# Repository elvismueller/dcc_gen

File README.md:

dcc_gen
=======

Simple DCC generator for ATMega8 (V2, schematics and board) and ATMega32 (V3-5, only protoypes) to control small isolated layouts.

Features:
- RS232 Interface (9600 baud) for debugging and simple control (use an normal USB to RS232 converter)
- Heartbeat LED should blink roundabout every 2 sek, fast blinking if waiting for second key
- Connect simple switches (ATMega8 10 inputs | ATMega32 4 groups, 20 Inputs, 80 switches in total)
- Support start-end logic and searches for routes in the internal memory
- Setup for USBProg ISP-Interface adapter by www.embeded-projecs.de (for any other modify platformio.ini)

Toolchain (PlatformIo)
- install Visual Studio Code
- install PlatformIO Extension via Extension Manager (left toolbar). Wait til its installed completely (Icon appears in left toolbar)!
- clone, pull and open workspace dcc_gen
- Build it (bottom bar tick icon)Toolchain
- install driver for USBasp with Zadig (https://zadig.akeo.ie/)
  == USBasp (HK version with fischl.de FW): more or less working with: WinUSB v6.1.7600 and libusb_win32, somehow unreliable
  == USBProg 3 running with modified config (check for platformio.ini)
- use "Upload" in Tasks by click on the PlatformIo Icon (Note: returns an error even if the upload was succesful), check avrdude output!

Toolchain Linux (_Archive)
- sudo aptitude install avr-libc avrdude gcc-avr simulavr
- check/use the Makefile

Kown issues: 
- it is NOT a central unit, just a simple generator
- a lot of hardcoded stuff, no SW to init the memory
- bare metal (no Ardunio Code)
- explizit build for either ATMega8 oder ATMega32
- tested only with a few turnout decoder (Claus Illchmann, LDT Datentechnik) some decoder are not working (QDecoder). 
- like almost all motorshields based on this hardware the generatet DCC signal is not recommended for train control. 
- the ATMega8 is very limited in memory and far less verbose (no help etc.)

Helpers
- read fuses with avrdude: .\avrdude -c avrispmkii -p atmega8 -U lfuse:r:-:i -v
- http://www.engbedded.com/fusecalc
- https://hendrich.org/blogs/mikrocontroller/atmega-644-fuses-setzen/
- programm size: C:/Users/EMM/.platformio/packages/toolchain-atmelavr/bin/avr-size --mcu=atmega8 -C .\firmware.elf

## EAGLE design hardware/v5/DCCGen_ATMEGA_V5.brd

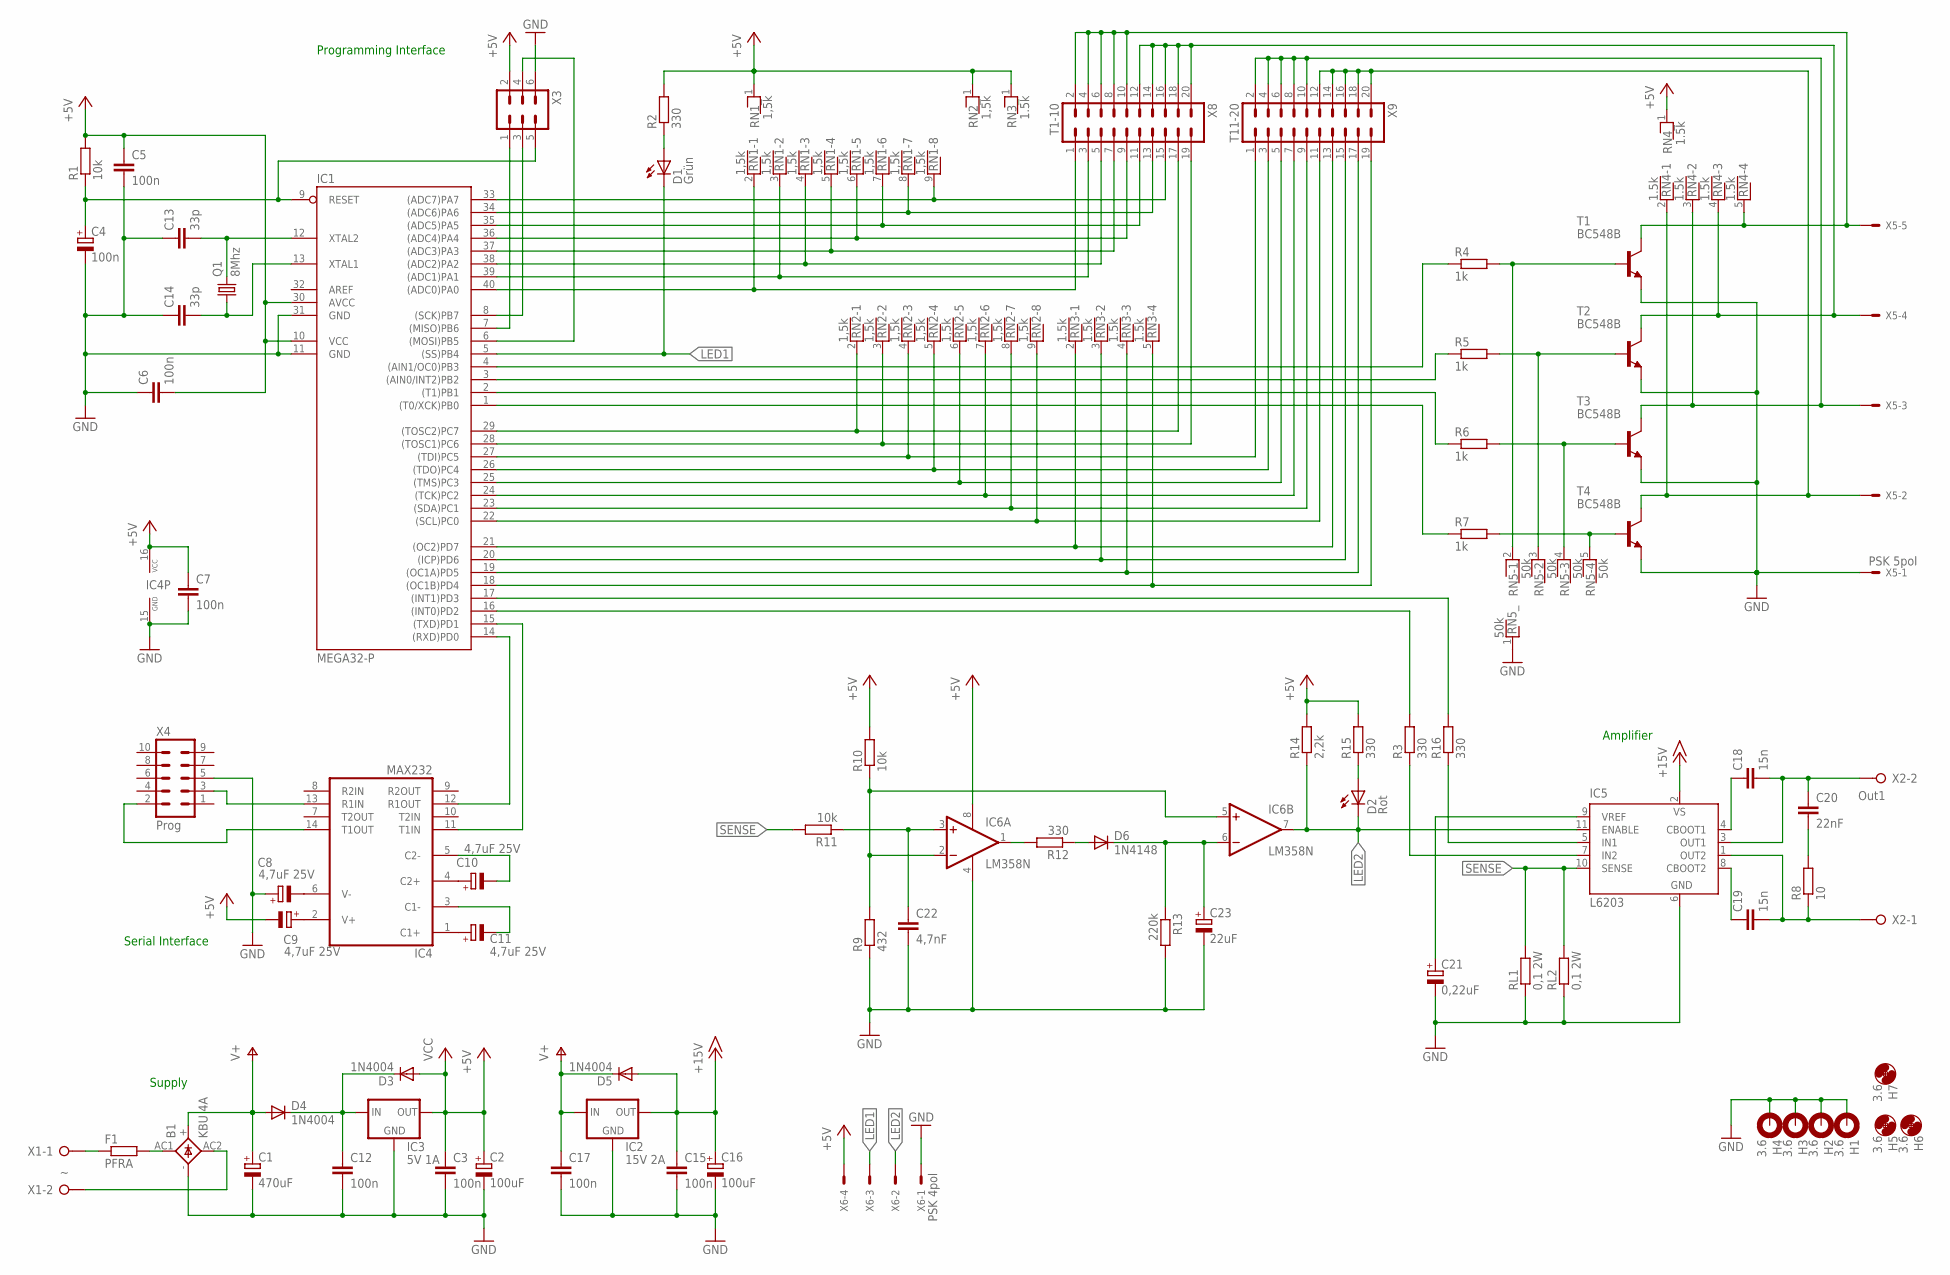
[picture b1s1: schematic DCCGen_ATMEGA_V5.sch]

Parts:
B1: KBU 4A; KBU
C1: 470uF; E5-13
C2, C16: 100uF; E2,5-7
C3, C5, C6, C7, C12, C15, C17: 100n; C025-025X050
C4: 100n; E2,5-5
C8, C9, C10, C11: 4,7uF 25V; E2,5-6E
C13, C14: 33p; C025-025X050
C18, C19: 15n; C025-025X050
C20: 22nF; C025-025X050
C21: 0,22uF; E2-5
C22: 4,7nF; C025-025X050
C23: 22uF; E2-5
D1: Grün; LED3MM
D2: Rot; LED3MM
D3, D4, D5: 1N4004; DO41-10
D6: 1N4148; DO35-10
F1: PFRA; 0204/5
H1, H2, H3, H4: 3.6; 3,6-PAD
H5, H6, H7: 3.6; 3,6
IC1: MEGA32-P; DIL40
IC2: 15V 2A; 78XXS
IC3: 5V 1A; 78XXS
IC4: MAX232; DIL16
IC5: L6203; MULTIWATT-11
IC6: LM358N; DIL08
Q1: 8Mhz; HC49U-V
R1, R10, R11: 10k; 0207/10
R2, R3, R12, R15, R16: 330; 0207/10
R4, R5, R6, R7: 1k; 0207/10
R8: 10; 0207/10
R9: 432; 0207/10
R13: 220k; 0207/10
R14: 2,2k; 0207/10
RL1, RL2: 0,1 2W; 0617/17
RN1, RN2: 1,5k; RN-9
RN3, RN4: 1.5k; RN-5
RN5: 50k; RN-5
T1, T2, T3, T4: BC548B; TO92-EBC
X1: W237-132
X2: Out1; W237-132
X3: ML6
X4: Prog; ML10
X5: PSK 5pol; 6410-05
X6: PSK 4pol; 6410-04
X8: T1-10; ML20
X9: T11-20; ML20

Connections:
+5V: C2.+, C3.1, C5.1, C6.2, C7.1, C9.-, D3.A, IC1.10 (VCC), IC1.30 (AVCC), IC3.OUT, IC4.16 (VCC), IC6.8 (V+), R1.2, R2.2, R10.2, R14.2, R15.2, RN1.1, RN2.1, RN3.1, RN4.1, X3.2, X6.4
+15V: C15.1, C16.+, D5.A, IC2.OUT, IC5.2 (VS)
GND: B1.-, C1.-, C2.-, C3.2, C4.-, C5.2, C6.1, C7.2, C8.+, C12.2, C13.1, C14.1, C15.2, C16.-, C17.2, C21.-, C22.2, C23.-, H1.B3,6, H2.B3,6, H3.B3,6, H4.B3,6, IC1.11 (GND), IC1.31 (GND), IC2.GND, IC3.GND, IC4.15 (GND), IC5.6 (GND), IC6.4 (V-), R9.1, R13.2, RL1.1, RL2.1, RN5.1, T1.E, T2.E, T3.E, T4.E, X3.6, X4.5, X5.1, X6.1
LED1: D1.K (C), IC1.5 ((SS)PB4), X6.3
LED2: D2.K (C), IC5.11 (ENABLE), IC6.7 (OUT), R14.1, X6.2
unnamed: F1.1, X1.1
unnamed: B1.AC2, X1.2
unnamed: IC1.6 ((MOSI)PB5), X3.4
unnamed: IC1.8 ((SCK)PB7), X3.3
unnamed: IC1.7 ((MISO)PB6), X3.1
unnamed: IC1.40 ((ADC0)PA0), RN1.2, X8.1
unnamed: IC1.39 ((ADC1)PA1), RN1.3, X8.3
unnamed: IC1.38 ((ADC2)PA2), RN1.4, X8.5
unnamed: C4.+, IC1.9 (RESET), R1.1, X3.5
unnamed: IC1.37 ((ADC3)PA3), RN1.5, X8.7
unnamed: IC1.36 ((ADC4)PA4), RN1.6, X8.9
unnamed: IC1.35 ((ADC5)PA5), RN1.7, X8.11
unnamed: IC1.34 ((ADC6)PA6), RN1.8, X8.13
unnamed: IC1.33 ((ADC7)PA7), RN1.9, X8.15
unnamed: C14.2, IC1.13 (XTAL1), Q1.1
unnamed: C12.1, D3.C, D4.C, IC3.IN
unnamed: D1.A, R2.1
unnamed: IC1.29 ((TOSC2)PC7), RN2.2, X8.17
unnamed: IC1.28 ((TOSC1)PC6), RN2.3, X8.19
unnamed: IC1.27 ((TDI)PC5), RN2.4, X9.1
unnamed: C21.+, IC5.9 (VREF)
unnamed: IC1.26 ((TDO)PC4), RN2.5, X9.3
unnamed: IC6.2 (-IN), IC6.5 (+IN), R9.2, R10.1
unnamed: C22.1, IC6.3 (+IN), R11.1
unnamed: C20.2, R8.2
unnamed: IC1.17 ((INT1)PD3), R16.2
unnamed: IC1.16 ((INT0)PD2), R3.2
unnamed: C18.2, C20.1, IC5.3 (OUT1), X2.2
unnamed: C18.1, IC5.4 (CBOOT1)
unnamed: IC1.15 ((TXD)PD1), IC4.11 (T1IN)
unnamed: IC1.14 ((RXD)PD0), IC4.12 (R1OUT)
unnamed: C8.-, IC4.6 (V-)
unnamed: C9.+, IC4.2 (V+)
unnamed: IC4.14 (T1OUT), X4.2
unnamed: C11.+, IC4.1 (C1+)
unnamed: C11.-, IC4.3 (C1-)
unnamed: C10.+, IC4.4 (C2+)
unnamed: C10.-, IC4.5 (C2-)
unnamed: IC4.13 (R1IN), X4.3
unnamed: IC1.25 ((TMS)PC3), RN2.6, X9.5
unnamed: B1.AC1, F1.2
unnamed: IC1.24 ((TCK)PC2), RN2.7, X9.7
unnamed: IC1.23 ((SDA)PC1), RN2.8, X9.9
unnamed: IC1.22 ((SCL)PC0), RN2.9, X9.11
unnamed: IC1.21 ((OC2)PD7), RN3.2, X9.13
unnamed: IC1.20 ((ICP)PD6), RN3.3, X9.15
unnamed: IC1.19 ((OC1A)PD5), RN3.4, X9.17
unnamed: IC1.18 ((OC1B)PD4), RN3.5, X9.19
unnamed: IC5.7 (IN2), R3.1
unnamed: IC5.5 (IN1), R16.1
unnamed: RN4.2, T4.C, X5.2, X9.12, X9.14, X9.16, X9.18, X9.20
unnamed: IC1.2 ((T1)PB1), R6.1
unnamed: IC1.1 ((T0/XCK)PB0), R7.1
unnamed: IC1.4 ((AIN1/OC0)PB3), R4.1
unnamed: IC1.3 ((AIN0/INT2)PB2), R5.1
unnamed: R4.2, RN5.2, T1.B
unnamed: R5.2, RN5.3, T2.B
unnamed: R6.2, RN5.4, T3.B
unnamed: R7.2, RN5.5, T4.B
unnamed: C13.2, IC1.12 (XTAL2), Q1.2
unnamed: C19.1, IC5.8 (CBOOT2)
unnamed: C19.2, IC5.1 (OUT2), R8.1, X2.1
unnamed: IC6.1 (OUT), R12.2
unnamed: C23.+, D6.C, IC6.6 (-IN), R13.1
unnamed: D6.A, R12.1
unnamed: RN4.5, T1.C, X5.5, X8.2, X8.4, X8.6, X8.8, X8.10
unnamed: RN4.4, T2.C, X5.4, X8.12, X8.14, X8.16, X8.18, X8.20
unnamed: RN4.3, T3.C, X5.3, X9.2, X9.4, X9.6, X9.8, X9.10
unnamed: D2.A, R15.1
SENSE: IC5.10 (SENSE), R11.2, RL1.2, RL2.2
V+: B1.+, C1.+, C17.1, D4.A, D5.C, IC2.IN

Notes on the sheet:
Serial Interface
Programming Interface
Amplifier
Supply

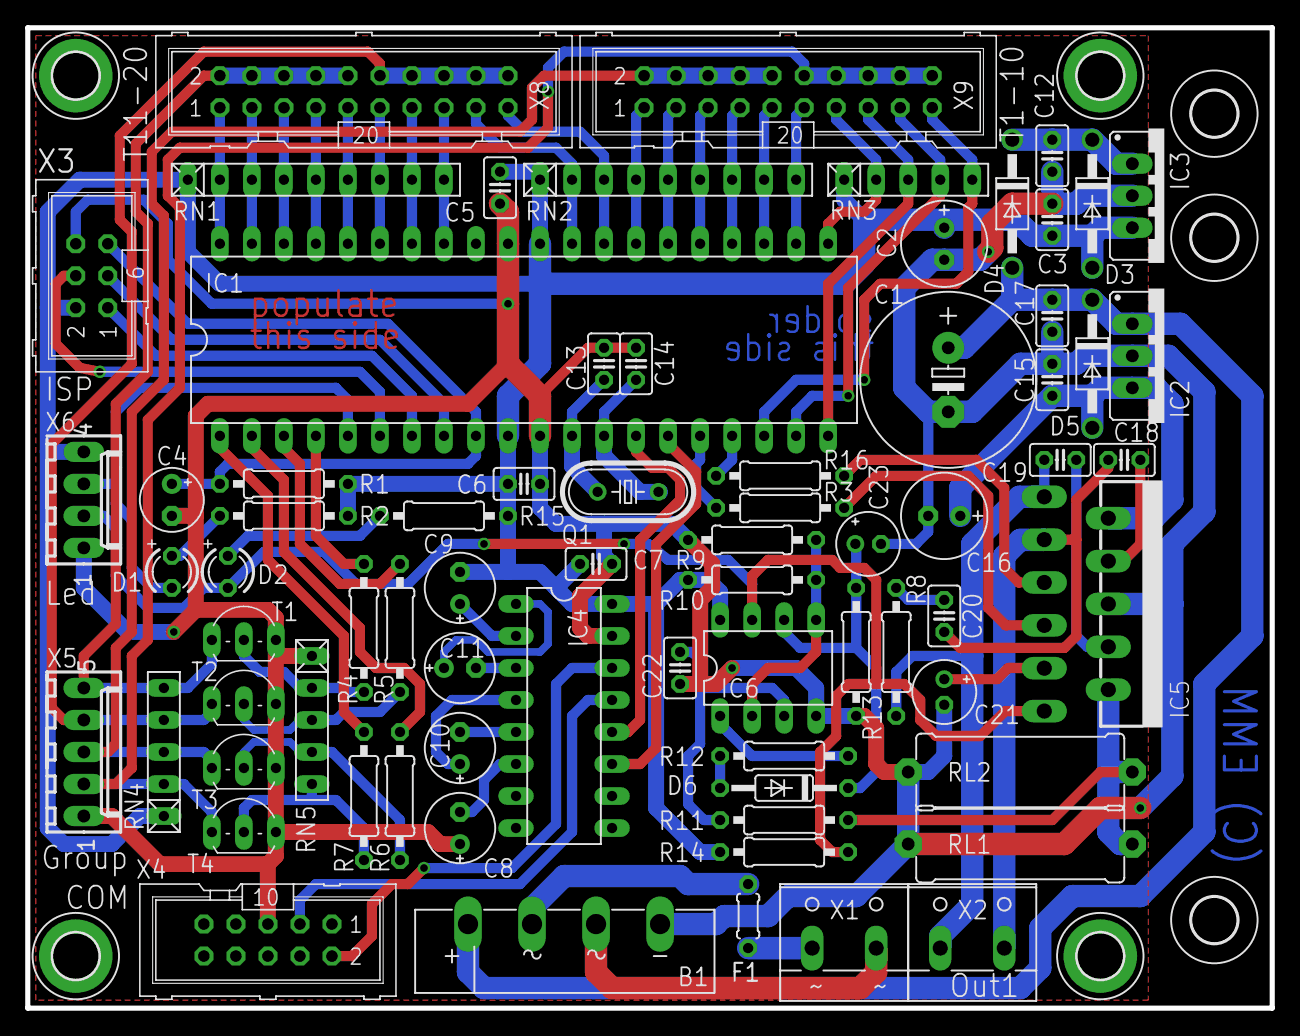
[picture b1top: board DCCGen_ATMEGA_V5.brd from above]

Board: 2 copper layers, 98.7 x 77.8 mm, 80 parts (0 on the bottom side), 76 nets.

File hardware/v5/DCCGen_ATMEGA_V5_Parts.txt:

Partlist

Exported from DCCGen_ATMEGA_V5.sch at 20.07.12 21:43

EAGLE Version 6.2.0 Copyright (c) 1988-2012 CadSoft

Assembly variant: 

Part     Value          Device             Package      Library             Sheet

B1       40V 1.5A       RB1A               RB1A         rectifier           1
C1       470uF          CPOL-EUE5-10.5     E5-10,5      rcl                 1
C2       100uF          CPOL-EUE2-5        E2-5         rcl                 1
C3       100n           C-EU025-025X050    C025-025X050 rcl                 1
C4       100n           CPOL-EUE2.5-5      E2,5-5       rcl                 1
C5       100n           C-EU025-025X050    C025-025X050 rcl                 1
C6       100n           C-EU025-025X050    C025-025X050 rcl                 1
C7       100n           C-EU025-025X050    C025-025X050 rcl                 1
C8       4,7uF 25V      CPOL-EUE2,5-6E     E2,5-6E      rcl                 1
C9       4,7uF 25V      CPOL-EUE2,5-6E     E2,5-6E      rcl                 1
C10      4,7uF 25V      CPOL-EUE2,5-6E     E2,5-6E      rcl                 1
C11      4,7uF 25V      CPOL-EUE2,5-6E     E2,5-6E      rcl                 1
C12      100n           C-EU025-025X050    C025-025X050 rcl                 1
C13      33p            C-EU025-025X050    C025-025X050 rcl                 1
C14      33p            C-EU025-025X050    C025-025X050 rcl                 1
C15      100n           C-EU025-025X050    C025-025X050 rcl                 1
C16      100uF          CPOL-EUE2-5        E2-5         rcl                 1
C17      100n           C-EU025-025X050    C025-025X050 rcl                 1
C18      15n            C-EU025-025X050    C025-025X050 rcl                 1
C19      15n            C-EU025-025X050    C025-025X050 rcl                 1
C20      22nF           C-EU025-025X050    C025-025X050 rcl                 1
C21      0,22uF         CPOL-EUE2-5        E2-5         rcl                 1
C22      4,7nF          C-EU025-025X050    C025-025X050 rcl                 1
C23      22uF           CPOL-EUE2-5        E2-5         rcl                 1
D1       Rot            LED3MM             LED3MM       led                 1
D2       1N4004         1N4004             DO41-10      diode               1
D3       1N4004         1N4004             DO41-10      diode               1
D4       1N4004         1N4004             DO41-10      diode               1
D5       1N4148         1N4148DO35-10      DO35-10      diode               1
D6       Rot            LED3MM             LED3MM       led                 1
F1       PFRA           R-EU_0204/5        0204/5       rcl                 1
H1       3.6            MOUNT-PAD-ROUND3.6 3,6-PAD      holes               1
H2       3.6            MOUNT-PAD-ROUND3.6 3,6-PAD      holes               1
H3       3.6            MOUNT-PAD-ROUND3.6 3,6-PAD      holes               1
H4       3.6            MOUNT-PAD-ROUND3.6 3,6-PAD      holes               1
IC1      MEGA32-P       MEGA32-P           DIL40        atmel               1
IC2      15V 2A         78XXS              78XXS        v-reg               1
IC3      MAX232         MAX232             DIL16        maxim               1
IC4      5V 1A          78XXS              78XXS        v-reg               1
IC5      L6203          L6203              MULTIWATT-11 st-microelectronics 1
IC6      LM358N         LM358N             DIL08        linear              1
Q1       8Mhz           CRYSTALHC49U-V     HC49U-V      crystal             1
R1       10k            R-EU_0207/10       0207/10      rcl                 1
R2       330            R-EU_0207/10       0207/10      rcl                 1
R3       330            R-EU_0207/10       0207/10      rcl                 1
R4       1k             R-EU_0207/10       0207/10      rcl                 1
R5       1k             R-EU_0207/10       0207/10      rcl                 1
R6       1k             R-EU_0207/10       0207/10      rcl                 1
R7       1k             R-EU_0207/10       0207/10      rcl                 1
R8       10             R-EU_0207/10       0207/10      rcl                 1
R9       432            R-EU_0207/10       0207/10      rcl                 1
R10      10k            R-EU_0207/10       0207/10      rcl                 1
R11      10k            R-EU_0207/10       0207/10      rcl                 1
R12      330            R-EU_0207/10       0207/10      rcl                 1
R13      220k           R-EU_0207/10       0207/10      rcl                 1
R16      2,2k           R-EU_0207/10       0207/10      rcl                 1
R17      330            R-EU_0207/10       0207/10      rcl                 1
RL1      0,1 2W         R-EU_0411/15       0411/15      rcl                 1
RL2      0,1 2W         R-EU_0411/15       0411/15      rcl                 1
RN1      1,5k           RNX8               RN-9         resistor-net        1
RN2      1,5k           RNX8               RN-9         resistor-net        1
RN3      1.5k           RNX4               RN-5         resistor-net        1
RN4      1.5k           RNX4               RN-5         resistor-net        1
RN5      50k            RNX4               RN-5         resistor-net        1
SJ1      Fuse           SJ                 SJ           jumper              1
SJ2      Fuse           SJ                 SJ           jumper              1
SJ7      0              SJ                 SJ           jumper              1
T1       BC548B         BC548B             TO92-EBC     transistor-npn      1
T2       BC548B         BC548B             TO92-EBC     transistor-npn      1
T3       BC548B         BC548B             TO92-EBC     transistor-npn      1
T4       BC548B         BC548B             TO92-EBC     transistor-npn      1
X1       ~              W237-02P           W237-132     con-wago-508        1
X2       Out1           W237-02P           W237-132     con-wago-508        1
X4       Prog           F09VP              F09VP        con-subd            1
X5       group          W237-05P           W237-5P      con-wago-508        1
X6       ISP            ML10               ML10         con-ml              1
X7       led            W237-02P           W237-132     con-wago-508        1
X8       T1-10          ML20               ML20         con-ml              1
X9       T11-20         ML20               ML20         con-ml              1

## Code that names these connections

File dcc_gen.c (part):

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#define	__AVR_ATmega32__	1

#ifdef __AVR_ATmega32__
 #define PIN_OUT1 PD2
 #define PIN_OUT2 PD3
#endif

#include "avr/io.h"
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  DDRD = 0x0;
  DDRC = 0x0;

  PORTC = 1<<PC5;	/* turn the LED off */
  DDRC = 1<<PC5;	/* PC5 as output - the LED is there */

  //care amplifier outputs
  PORTB |= 1<<PB0;	/* Output A LOW  */
  DDRB |= 1<<PB0;	/* PB0 as output */
  PORTB |= 1<<PB1;	/* Output B LOW  */
  DDRB |= 1<<PB1;	/* PB1 as output */
#endif

#ifdef __AVR_ATmega32__
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  DDRD = 0x0;

  //care LED port
  PORTB |= 1<<PB4;
  DDRB |= 1<<PB4;

  //care amplifier outputs
  PORTD |= 1<<PIN_OUT1;	/* Output A LOW  */
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  switch (state)
  {
  case 0:
    PORTB &= ~(1<<PB4);
    break;
  case 1:
    PORTB |= 1<<PB4;
    break;
  default:
    if (PORTB & 1<<PB4)
      PORTB &= ~(1<<PB4);
    else
      PORTB |= 1<<PB4;
  }
#endif
}
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{ //temps
  char cLimit = 10;
  //check inputs
  if (PINC & (1<<PC0)) {if (cKey[0]>0) cKey[0]--; } else {if (cKey[0]<cLimit) cKey[0]++;}
  if (PINC & (1<<PC1)) {if (cKey[1]>0) cKey[1]--; } else {if (cKey[1]<cLimit) cKey[1]++;}
  if (PINC & (1<<PC2)) {if (cKey[2]>0) cKey[2]--; } else {if (cKey[2]<cLimit) cKey[2]++;}
  if (PINC & (1<<PC3)) {if (cKey[3]>0) cKey[3]--; } else {if (cKey[3]<cLimit) cKey[3]++;}
  if (PINC & (1<<PC4)) {if (cKey[4]>0) cKey[4]--; } else {if (cKey[4]<cLimit) cKey[4]++;}
  if (PIND & (1<<PD3)) {if (cKey[5]>0) cKey[5]--; } else {if (cKey[5]<cLimit) cKey[5]++;}
  if (PIND & (1<<PD4)) {if (cKey[6]>0) cKey[6]--; } else {if (cKey[6]<cLimit) cKey[6]++;}
  if (PIND & (1<<PD5)) {if (cKey[7]>0) cKey[7]--; } else {if (cKey[7]<cLimit) cKey[7]++;}
  if (PIND & (1<<PD6)) {if (cKey[8]>0) cKey[8]--; } else {if (cKey[8]<cLimit) cKey[8]++;}
  if (PIND & (1<<PD7)) {if (cKey[9]>0) cKey[9]--; } else {if (cKey[9]<cLimit) cKey[9]++;}
}

char KeybIsKey(unsigned char Index)
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{ char ret = false;
  switch (index)
  { 
    case  0: ret = (PINA & (1<<PA0)); break;
    case  1: ret = (PINA & (1<<PA1)); break;
    case  2: ret = (PINA & (1<<PA2)); break;
    case  3: ret = (PINA & (1<<PA3)); break;
    case  4: ret = (PINA & (1<<PA4)); break;
    case  5: ret = (PINA & (1<<PA5)); break;
    case  6: ret = (PINA & (1<<PA6)); break;
    case  7: ret = (PINA & (1<<PA7)); break;
    case  8: ret = (PINC & (1<<PC7)); break;
    case  9: ret = (PINC & (1<<PC6)); break;
    case 10: ret = (PINC & (1<<PC5)); break;
    case 11: ret = (PINC & (1<<PC4)); break;
    case 12: ret = (PINC & (1<<PC3)); break;
    case 13: ret = (PINC & (1<<PC2)); break;
    case 14: ret = (PINC & (1<<PC1)); break;
    case 15: ret = (PINC & (1<<PC0)); break;
    case 16: ret = (PIND & (1<<PD7)); break;
    case 17: ret = (PIND & (1<<PD6)); break;
    case 18: ret = (PIND & (1<<PD5)); break;
    case 19: ret = (PIND & (1<<PD4)); break;
    default: ret = false;
  }
  return ret;
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  switch (keybActiveGroup) 
  {
  case 0:
    PORTB |=  (1<<PB0);
    PORTB &= ~(1<<PB1);
    PORTB &= ~(1<<PB2);
    PORTB &= ~(1<<PB3);
    break;
  case 1:
    PORTB &= ~(1<<PB0);
    PORTB |=  (1<<PB1);
    PORTB &= ~(1<<PB2);
    PORTB &= ~(1<<PB3);
    break;
  case 2:
    PORTB &= ~(1<<PB0);
    PORTB &= ~(1<<PB1);
    PORTB |=  (1<<PB2);
    PORTB &= ~(1<<PB3);
    break;
  case 3:
    PORTB &= ~(1<<PB0);
    PORTB &= ~(1<<PB1);
    PORTB &= ~(1<<PB2);
    PORTB |=  (1<<PB3);
    break;
  }
  return;
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
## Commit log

2020-01-29 intial from old version
2020-01-29 probably last version
2020-04-10 port to VS Code and platformIO
2020-04-17 add workspace, add fuses
2020-04-17 fix string usage for small cpus, fix warnings
2022-04-28 Get it running again in Platform.io, fix DCC switch command (works now with SandEi, digital-bahn.de). Kown issue in UART: does not answer correctly
2022-05-02 refactor state machine, fix memory and UART
2023-12-21 add parameter to switch off idle toggle, add toggle for switches, fix delays, optimize flash
2023-12-21 fix merge, checked with Arduino DCC decoder
2023-12-23 add hardware
2023-12-23 add config for ATMega32, checked with v5 board
2023-12-26 add docu for Stapelmueller
